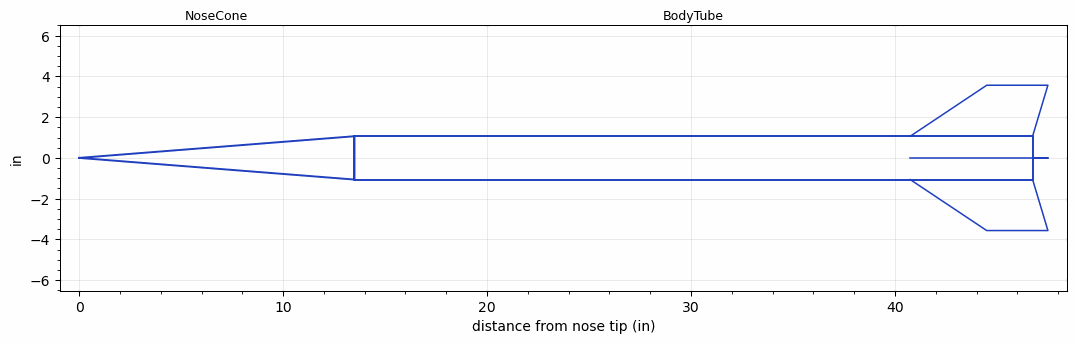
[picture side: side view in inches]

<RASAeroDocument>
 <FileVersion>2</FileVersion>
 <RocketDesign>
  <NoseCone>
   <Length>13.5</Length>
   <Diameter>2.125</Diameter>
   <Shape>Conical</Shape>
   <Location>0</Location>
  </NoseCone>
  <BodyTube>
   <Length>33.25</Length>
   <Diameter>2.125</Diameter>
   <Location>13.5</Location>
   <Fin>
    <Count>4</Count>
    <Chord>6</Chord>
    <Span>2.5</Span>
    <SweepDistance>3.75</SweepDistance>
    <TipChord>3</TipChord>
    <Thickness>0.138</Thickness>
    <LERadius>0.001</LERadius>
    <Location>6</Location>
    <AirfoilSection>Hexagonal</AirfoilSection>
    <FX1>1.1875</FX1>
    <FX3>1.1875</FX3>
   </Fin>
  </BodyTube>
  <Surface>Rough Camouflage Paint</Surface>
  <ModifiedBarrowman>True</ModifiedBarrowman>
  <Turbulence>True</Turbulence>
  <UseBooster1>False</UseBooster1>
  <UseBooster2>False</UseBooster2>
 </RocketDesign>
 <LaunchSite>
  <Altitude>2000</Altitude>
  <Pressure>0</Pressure>
  <RodAngle>0</RodAngle>
  <RodLength>4</RodLength>
  <Temperature>74</Temperature>
  <WindSpeed>0</WindSpeed>
 </LaunchSite>
 <Recovery>
  <Altitude1>1000</Altitude1>
  <Altitude2>1000</Altitude2>
  <DeviceType1>None</DeviceType1>
  <DeviceType2>None</DeviceType2>
  <Event1>False</Event1>
  <Event2>False</Event2>
  <Size1>1</Size1>
  <Size2>1</Size2>
  <EventType1>None</EventType1>
  <EventType2>None</EventType2>
  <CD1>1.33</CD1>
  <CD2>1.33</CD2>
 </Recovery>
 <SimulationList>
  <Simulation>
   <SustainerEngine>L2223  (MYA)</SustainerEngine>
   <SustainerLaunchWt>5.56</SustainerLaunchWt>
   <SustainerCG>29.04</SustainerCG>
   <SustainerIgnitionDelay>0</SustainerIgnitionDelay>
   <Booster1SeparationDelay>0</Booster1SeparationDelay>
   <Booster1IgnitionDelay>0</Booster1IgnitionDelay>
   <IncludeBooster1>False</IncludeBooster1>
   <Booster2Delay>0</Booster2Delay>
   <IncludeBooster2>False</IncludeBooster2>
   <TimetoApogee>23.12043</TimetoApogee>
   <MaxAltitude>19168.98</MaxAltitude>
   <MaxVelocity>4687.781</MaxVelocity>
  </Simulation>
 </SimulationList>
</RASAeroDocument>
